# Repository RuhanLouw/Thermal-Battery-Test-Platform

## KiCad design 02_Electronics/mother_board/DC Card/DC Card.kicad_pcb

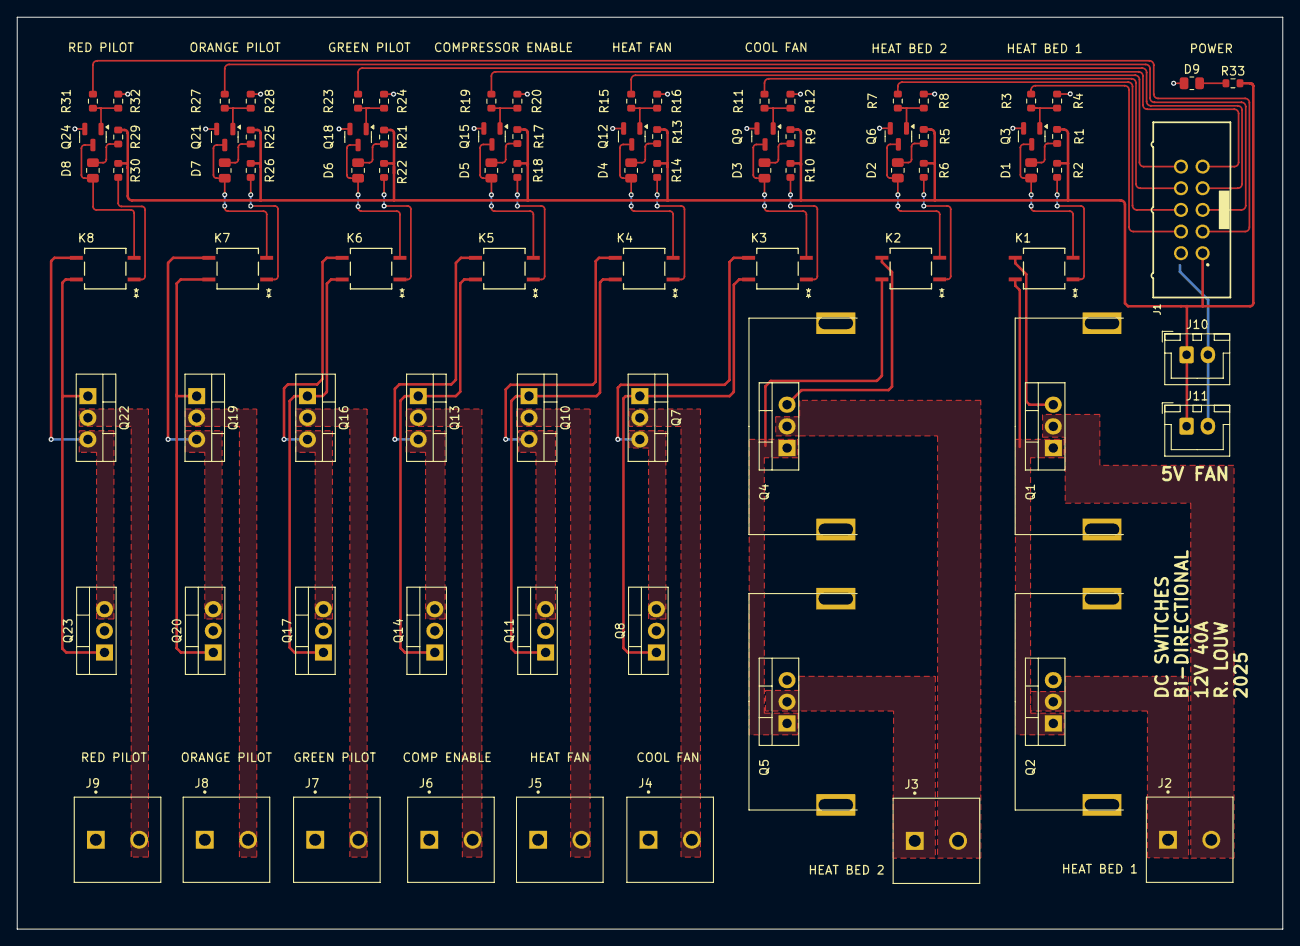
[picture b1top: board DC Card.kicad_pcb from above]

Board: 2 copper layers, 148.5 x 107.0 mm, 85 parts (0 on the bottom side), 75 nets.

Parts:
D1, D2, D3, D4, D5, D6, D7, D8, D9: LED; R_0805_2012Metric
J1: 61201021621
J2, J3, J4, J5, J6, J7, J8, J9: SW Conn; TE_282857-2_screw
J10, J11: Conn_01x02; JST_XH_B2B-XH-A_1x02_P2.50mm_Vertical
K1, K2, K3, K4, K5, K6, K7, K8: APV1121S; SOP4PIN_PAN-M
Q1, Q2, Q4, Q5: IRFB7545PBF; HSS-B20-NPR-02 heatsink
Q3, Q6, Q9, Q12, Q15, Q18, Q21, Q24: BSS138L; SOT-23
Q7, Q8, Q10, Q11, Q13, Q14, Q16, Q17, Q19, Q20, Q22, Q23: IRFB7545PBF; TO-220-3_Vertical
R1, R5, R9, R13, R17, R21, R25, R29: 145; R_0603_1608Metric
R2, R6, R10, R14, R18, R22, R26, R30: 182; R_0603_1608Metric
R3, R7, R11, R15, R19, R23, R27, R31: 300; R_0603_1608Metric
R4, R8, R12, R16, R20, R24, R28, R32: 10k; R_0603_1608Metric
R33: 150; R_0603_1608Metric

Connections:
5V_{DD}: J1.1, J10.1, J11.1, R1.2, R2.1, R5.2, R6.1, R9.2, R10.1, R13.2, R14.1, R17.2, R18.1, R21.2, R22.1, R25.2, R26.1, R29.2, R30.1, R33.2
/DC Switch_1/SWa: J3.1, Q5.2 (D)
/DC Switch_1/SWb: J3.2, Q4.2 (D)
/DC Switch_2/SWa: J4.1, Q8.2 (D)
/DC Switch_2/SWb: J4.2, Q7.2 (D)
/DC Switch_3/SWa: J5.1, Q11.2 (D)
/DC Switch_3/SWb: J5.2, Q10.2 (D)
/DC Switch_4/SWa: J6.1, Q14.2 (D)
/DC Switch_4/SWb: J6.2, Q13.2 (D)
/DC Switch_5/SWa: J7.1, Q17.2 (D)
/DC Switch_5/SWb: J7.2, Q16.2 (D)
/DC Switch_6/SWa: J8.1, Q20.2 (D)
/DC Switch_6/SWb: J8.2, Q19.2 (D)
/DC Switch_7/SWa: J9.1, Q23.2 (D)
/DC Switch_7/SWb: J9.2, Q22.2 (D)
/DC Switch_/SWa: J2.1, Q2.2 (D)
/DC Switch_/SWb: J2.2, Q1.2 (D)
DC Comp _EN: J1.9, R19.1
Evap FAN _PWM: J1.8, R11.1
GND_{DD}: D9.1 (K), J1.2, J10.2, J11.2, Q3.2 (S), Q6.2 (S), Q9.2 (S), Q12.2 (S), Q15.2 (S), Q18.2 (S), Q21.2 (S), Q24.2 (S), R4.2, R8.2, R12.2, R16.2, R20.2, R24.2, R28.2, R32.2
GREEN_PILOT _EN: J1.7, R23.1
HeatBed FAN _PWM: J1.10, R15.1
HeatBed_1 _PWM: J1.4, R3.1
HeatBed_2 _PWM: J1.6, R7.1
unnamed: D1.2 (A), R1.1
unnamed: D1.1 (K), K1.2, Q3.3 (D)
unnamed: D2.2 (A), R5.1
unnamed: D2.1 (K), K2.2, Q6.3 (D)
unnamed: D3.2 (A), R9.1
unnamed: D3.1 (K), K3.2, Q9.3 (D)
unnamed: D4.2 (A), R13.1
unnamed: D4.1 (K), K4.2, Q12.3 (D)
unnamed: D5.2 (A), R17.1
unnamed: D5.1 (K), K5.2, Q15.3 (D)
unnamed: D6.2 (A), R21.1
unnamed: D6.1 (K), K6.2, Q18.3 (D)
unnamed: D7.2 (A), R25.1
unnamed: D7.1 (K), K7.2, Q21.3 (D)
unnamed: D8.2 (A), R29.1
unnamed: D8.1 (K), K8.2, Q24.3 (D)
unnamed: D9.2 (A), R33.1
unnamed: K1.1, R2.2
unnamed: K2.1, R6.2
unnamed: K3.1, R10.2
unnamed: K4.1, R14.2
unnamed: K5.1, R18.2
unnamed: K6.1, R22.2
unnamed: K7.1, R26.2
unnamed: K8.1, R30.2
unnamed: K1.4, Q1.1 (G), Q2.1 (G)
unnamed: K1.3, Q1.3 (S), Q2.3 (S)
unnamed: Q3.1 (G), R3.2, R4.1
unnamed: K2.4, Q4.1 (G), Q5.1 (G)
unnamed: K2.3, Q4.3 (S), Q5.3 (S)
unnamed: Q6.1 (G), R7.2, R8.1
unnamed: K3.4, Q7.1 (G), Q8.1 (G)
unnamed: K3.3, Q7.3 (S), Q8.3 (S)
unnamed: Q9.1 (G), R11.2, R12.1
unnamed: K4.4, Q10.1 (G), Q11.1 (G)
unnamed: K4.3, Q10.3 (S), Q11.3 (S)
unnamed: Q12.1 (G), R15.2, R16.1
unnamed: K5.4, Q13.1 (G), Q14.1 (G)
unnamed: K5.3, Q13.3 (S), Q14.3 (S)
unnamed: Q15.1 (G), R19.2, R20.1
unnamed: K6.4, Q16.1 (G), Q17.1 (G)
unnamed: K6.3, Q16.3 (S), Q17.3 (S)
unnamed: Q18.1 (G), R23.2, R24.1
unnamed: K7.4, Q19.1 (G), Q20.1 (G)
unnamed: K7.3, Q19.3 (S), Q20.3 (S)
unnamed: Q21.1 (G), R27.2, R28.1
unnamed: K8.4, Q22.1 (G), Q23.1 (G)
unnamed: K8.3, Q22.3 (S), Q23.3 (S)
unnamed: Q24.1 (G), R31.2, R32.1
ORANGE_PILOT _EN: J1.5, R27.1
RED_PILOT _EN: J1.3, R31.1

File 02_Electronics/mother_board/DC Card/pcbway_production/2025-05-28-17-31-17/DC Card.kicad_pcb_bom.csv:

Designator,Quantity,Value,Footprint,Package,MPN,DNP,Mount_Type,Description
"D1, D2, D3, D4, D5, D6, D7, D8, D9",9,LED,R_0805_2012Metric,,,,smt,LED RED CLEAR 0805 SMD
J1,1,61201021621,61201021621,,,,tht,"Connector Header Through Hole 10 position 0.100"" (2.54mm)"
"J10, J11",2,Conn_01x02,JST_XH_B2B-XH-A_1x02_P2.50mm_Vertical,,,,tht,"Generic connector, single row, 01x02, script generated (kicad-library-utils/schlib/autogen/connector/)"
"J2, J3, J4, J5, J6, J7, J8, J9",8,SW Conn,TE_282857-2_screw,,,,tht,"Generic screw terminal, single row, 01x02, script generated (kicad-library-utils/schlib/autogen/connector/)"
"K1, K2, K3, K4, K5, K6, K7, K8",8,APV1121S,SOP4PIN_PAN-M,,,,smt,Optoisolator Photovoltaic Output 2500Vrms 1 Channel 4-SOP
"Q1, Q2, Q4, Q5",4,IRFB7545PBF,HSS-B20-NPR-02 heatsink,,,,tht,N-Channel 60 V 95A (Tc) 125W (Tc) Through Hole TO-220
"Q10, Q11, Q13, Q14, Q16, Q17, Q19, Q20, Q22, Q23, Q7, Q8",12,IRFB7545PBF,TO-220-3_Vertical,,,,tht,N-Channel 60 V 95A (Tc) 125W (Tc) Through Hole TO-220
"Q12, Q15, Q18, Q21, Q24, Q3, Q6, Q9",8,BSS138L,SOT-23,,,,smt,"50V Vds, 0.22A Id, N-Channel MOSFET, SOT-23"
"R1, R13, R17, R21, R25, R29, R5, R9",8,145,R_0603_1608Metric,,,,smt,RES 145 OHM 0.5% 1/10W 0603
"R10, R14, R18, R2, R22, R26, R30, R6",8,182,R_0603_1608Metric,,,,smt,RES 182 OHM 1% 1/10W 0603
"R11, R15, R19, R23, R27, R3, R31, R7",8,300,R_0603_1608Metric,,,,smt,RES SMD 300 OHM 5% 1/10W 0603
"R12, R16, R20, R24, R28, R32, R4, R8",8,10k,R_0603_1608Metric,,,,smt,RES 10K OHM 1% 1/10W 0603
R33,1,150,R_0603_1608Metric,,,,smt,RES SMD 150 OHM 0.1% 1/10W 0603

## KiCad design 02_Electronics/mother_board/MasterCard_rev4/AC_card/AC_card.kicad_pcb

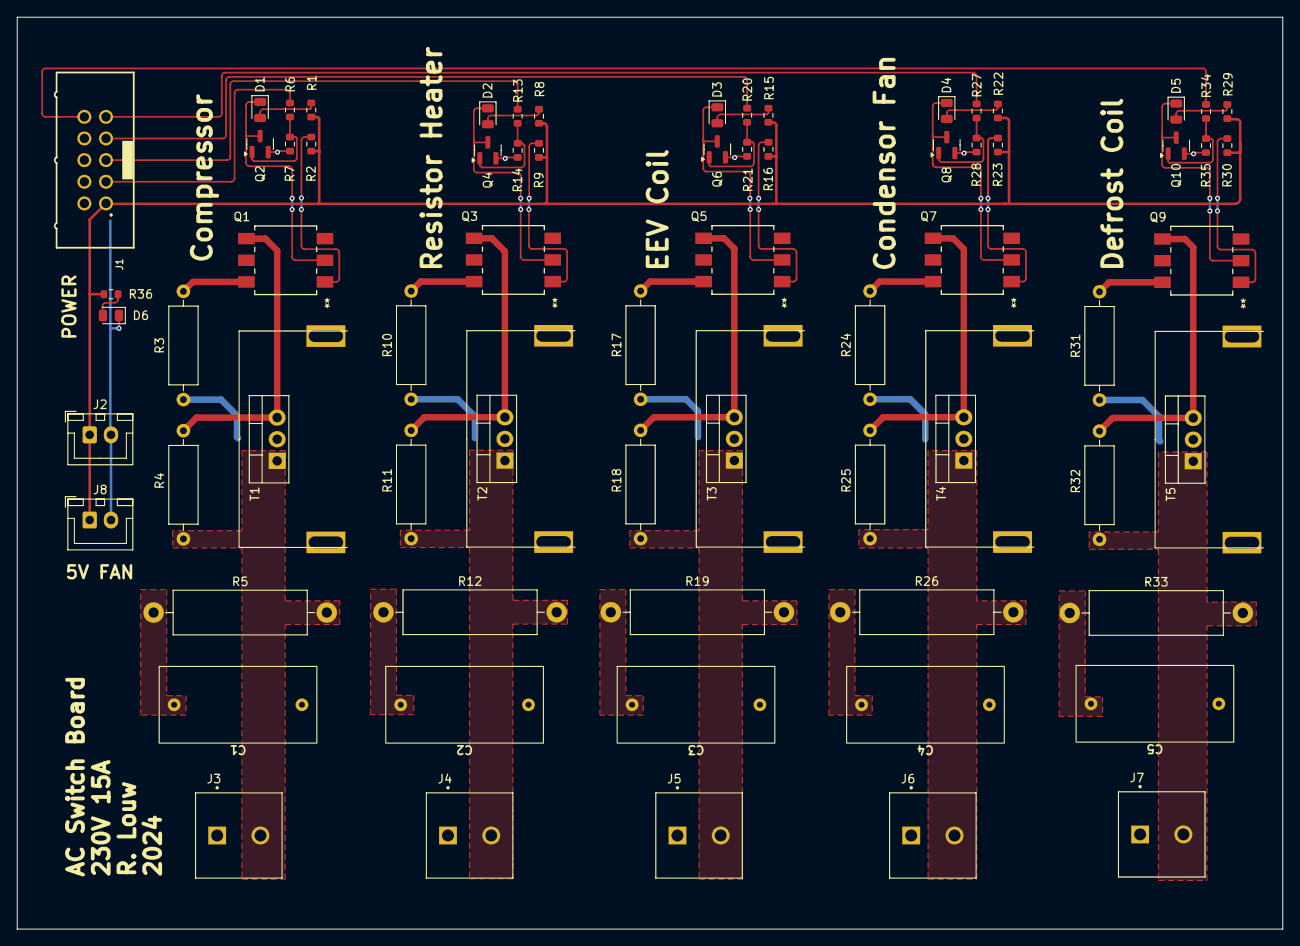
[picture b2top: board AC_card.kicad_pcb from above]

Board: 2 copper layers, 148.5 x 107.0 mm, 70 parts (0 on the bottom side), 53 nets.

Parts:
C1, C2, C3, C4, C5: 0.22u; CAP FILM 0.22UF 10 800VDC RAD
D1, D2, D3, D4, D5, D6: LED RED CLEAR 0805 SMD; LED_0805_2012Metric
J1: Control IN; 61201021621
J2, J8: Fan; JST_XH_B2B-XH-A_1x02_P2.50mm_Vertical
J3, J4, J5, J6, J7: Screw_Terminal_01x02; TE_282857-2_screw
Q1, Q3, Q5, Q7, Q9: MOC3063S-TA1; MOC306XS_LTO
Q2, Q4, Q6, Q8, Q10: BSS138L; SOT-23
R1, R8, R15, R22, R29, R36: 145; R_0603_1608Metric
R2, R9, R16, R23, R30: 182; R_0603_1608Metric
R3, R10, R17, R24, R31: 100; R_Axial_DIN0309_L9.0mm_D3.2mm_P12.70mm_Horizontal
R4, R11, R18, R25, R32: 390; R_Axial_DIN0309_L9.0mm_D3.2mm_P12.70mm_Horizontal
R5, R12, R19, R26, R33: 51; R_Axial_DIN0516_L15.5mm_D5.0mm_P20.32mm_Horizontal
R6, R13, R20, R27, R34: 300; R_0603_1608Metric
R7, R14, R21, R28, R35: 10k; R_0603_1608Metric
T1, T2, T3, T4, T5: BT138-800E,127; HSS-B20-NPR-02 heatsink

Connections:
5V_{DD}: J1.1, J2.1, J8.1, R1.2, R2.1, R8.2, R9.1, R15.2, R16.1, R22.2, R23.1, R29.2, R30.1, R36.2
/AC_SWITCH1/230VAC: C2.2, J4.1, R10.1, T2.2
/AC_SWITCH1/LOAD: J4.2, R11.2, R12.2, T2.1
/AC_SWITCH2/230VAC: C3.2, J5.1, R17.1, T3.2
/AC_SWITCH2/LOAD: J5.2, R18.2, R19.2, T3.1
/AC_SWITCH3/230VAC: C4.2, J6.1, R24.1, T4.2
/AC_SWITCH3/LOAD: J6.2, R25.2, R26.2, T4.1
/AC_SWITCH4/230VAC: C5.2, J7.1, R31.1, T5.2
/AC_SWITCH4/LOAD: J7.2, R32.2, R33.2, T5.1
/AC_SWITCH/230VAC: C1.2, J3.1, R3.1, T1.2
/AC_SWITCH/LOAD: J3.2, R4.2, R5.2, T1.1
AC COMP ENABLE: J1.3, R6.1
AC DEFROST ENABLE: J1.10, R34.1
AC EEV COIL ENABLE: J1.7, R20.1
AC FAN ENABLE: J1.9, R27.1
AC HEATER RESISTOR ENABLE: J1.5, R13.1
GND_{DD}: D6.1 (K), J1.2, J2.2, J8.2, Q2.2 (S), Q4.2 (S), Q6.2 (S), Q8.2 (S), Q10.2 (S), R7.2, R14.2, R21.2, R28.2, R35.2
unnamed: C1.1, R5.1
unnamed: C2.1, R12.1
unnamed: C3.1, R19.1
unnamed: C4.1, R26.1
unnamed: C5.1, R33.1
unnamed: D1.2 (A), R1.1
unnamed: D1.1 (K), Q1.2, Q2.3 (D)
unnamed: D2.2 (A), R8.1
unnamed: D2.1 (K), Q3.2, Q4.3 (D)
unnamed: D3.2 (A), R15.1
unnamed: D3.1 (K), Q5.2, Q6.3 (D)
unnamed: D4.2 (A), R22.1
unnamed: D4.1 (K), Q7.2, Q8.3 (D)
unnamed: D5.2 (A), R29.1
unnamed: D5.1 (K), Q9.2, Q10.3 (D)
unnamed: D6.2 (A), R36.1
unnamed: Q1.1, R2.2
unnamed: Q1.4, R4.1, T1.3
unnamed: Q1.6, R3.2
unnamed: Q2.1 (G), R6.2, R7.1
unnamed: Q3.1, R9.2
unnamed: Q3.4, R11.1, T2.3
unnamed: Q3.6, R10.2
unnamed: Q4.1 (G), R13.2, R14.1
unnamed: Q5.1, R16.2
unnamed: Q5.4, R18.1, T3.3
unnamed: Q5.6, R17.2
unnamed: Q6.1 (G), R20.2, R21.1
unnamed: Q7.1, R23.2
unnamed: Q7.4, R25.1, T4.3
unnamed: Q7.6, R24.2
unnamed: Q8.1 (G), R27.2, R28.1
unnamed: Q9.1, R30.2
unnamed: Q9.4, R32.1, T5.3
unnamed: Q9.6, R31.2
unnamed: Q10.1 (G), R34.2, R35.1

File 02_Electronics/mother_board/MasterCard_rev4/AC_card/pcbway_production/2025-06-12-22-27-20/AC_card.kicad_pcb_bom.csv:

Designator,Quantity,Value,Footprint,Package,MPN,DNP,Mount_Type,Description,PARTREV,STANDARD,MAXIMUM_PACKAGE_HEIGHT,MANUFACTURER
"C1, C2, C3, C4, C5",5,0.22u,CAP FILM 0.22UF 10 800VDC RAD,,,,tht,"0.22 µF Film Capacitor 650V 1600V (1.6kV) Polypropylene (PP), Metallized Radial",,,,
"D1, D2, D3, D4, D5, D6",6,LED RED CLEAR 0805 SMD,LED_0805_2012Metric,,,,smt,Red 625nm LED Indication - Discrete 2V 0805 (2012 Metric),,,,
J1,1,Control IN,61201021621,,,,tht,"Connector Header Through Hole 10 position 0.100"" (2.54mm)",,,,
"J2, J8",2,Fan,JST_XH_B2B-XH-A_1x02_P2.50mm_Vertical,,,,tht,"Generic connector, single row, 01x02, script generated (kicad-library-utils/schlib/autogen/connector/)",,,,
"J3, J4, J5, J6, J7",5,Screw_Terminal_01x02,TE_282857-2_screw,,,,tht,"Generic screw terminal, single row, 01x02, script generated (kicad-library-utils/schlib/autogen/connector/)",,,,
"Q1, Q3, Q5, Q7, Q9",5,MOC3063S-TA1,MOC306XS_LTO,,,,smt,,,,,
"Q10, Q2, Q4, Q6, Q8",5,BSS138L,SOT-23,,,,smt,MOSFET N-CH 50V 200MA SOT23-3,,,,
"R1, R15, R22, R29, R36, R8",6,145,R_0603_1608Metric,,,,smt,RES 145 OHM 0.5% 1/10W 0603,,,,
"R10, R17, R24, R3, R31",5,100,R_Axial_DIN0309_L9.0mm_D3.2mm_P12.70mm_Horizontal,,,,tht,"100 Ohms ±5% 0.5W, 1/2W Through Hole Resistor Axial Carbon Film",,,,
"R11, R18, R25, R32, R4",5,390,R_Axial_DIN0309_L9.0mm_D3.2mm_P12.70mm_Horizontal,,,,tht,RES 390 OHM 5% 1/2W AXIAL,,,,
"R12, R19, R26, R33, R5",5,51,R_Axial_DIN0516_L15.5mm_D5.0mm_P20.32mm_Horizontal,,,,tht,"51 Ohms ±5% 3W Through Hole Resistor Axial Flame Retardant Coating, Pulse Withstanding, Safety Metal Film",,,,
"R13, R20, R27, R34, R6",5,300,R_0603_1608Metric,,,,smt,RES SMD 300 OHM 5% 1/10W 0603,,,,
"R14, R21, R28, R35, R7",5,10k,R_0603_1608Metric,,,,smt,RES 10K OHM 1% 1/10W 0603,,,,
"R16, R2, R23, R30, R9",5,182,R_0603_1608Metric,,,,smt,RES 182 OHM 1% 1/10W 0603,,,,
"T1, T2, T3, T4, T5",5,"BT138-800E,127",HSS-B20-NPR-02 heatsink,,,,tht,TRIAC SENS GATE 800V 12A TO220AB,02,IPC 7351B,19.35 mm,WeEn Semiconductors

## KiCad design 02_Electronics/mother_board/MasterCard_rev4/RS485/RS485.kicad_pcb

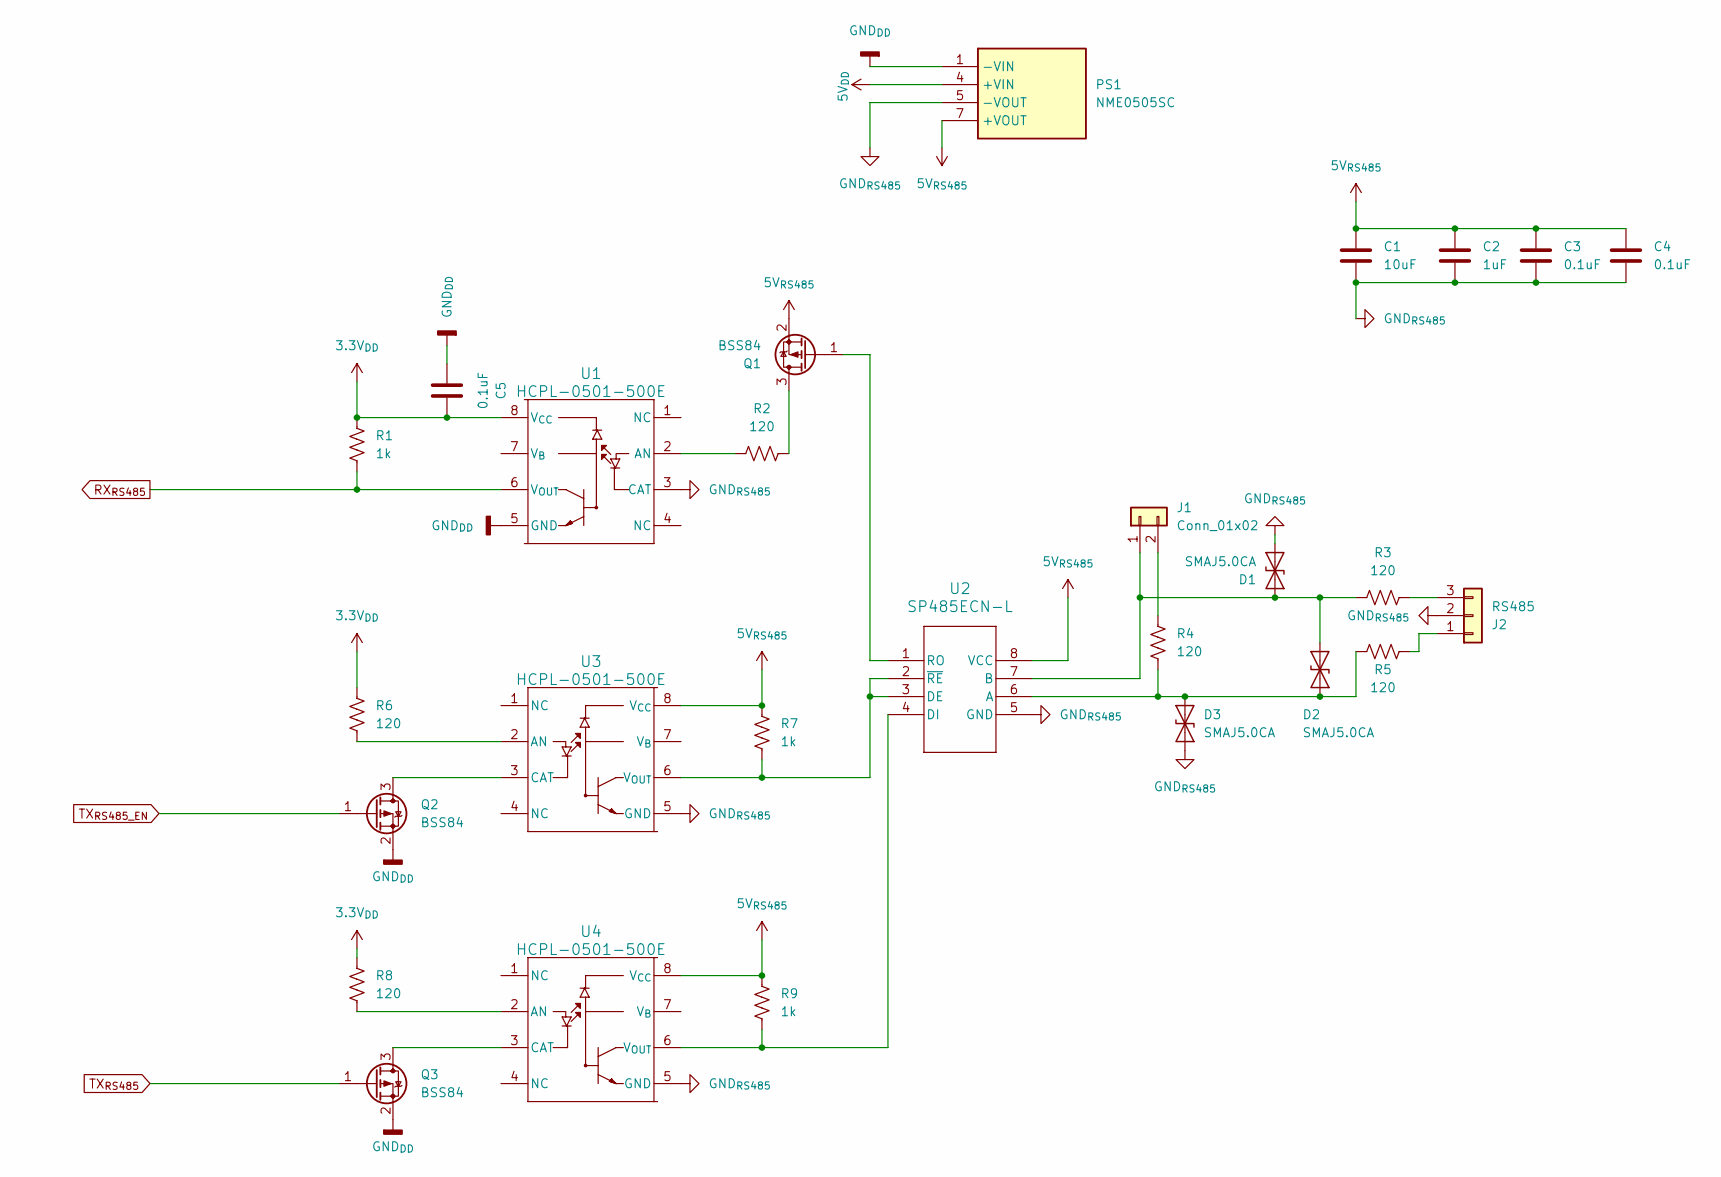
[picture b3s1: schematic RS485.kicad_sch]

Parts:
C1: 10uF; C_0805_2012Metric
C2: 1uF; C_0603_1608Metric
C3, C4, C5: 0.1uF; C_0603_1608Metric
D1, D2, D3: SMAJ5.0CA; D_SMA
J1: Conn_01x02; PinHeader_1x02_P2.54mm_Vertical
J2: RS485; TE_282857-3_screw
PS1: NME0505SC; Mouser Part Number 580-NME0505SC
Q1, Q2, Q3: BSS84; SOT-23
R1, R7, R9: 1k; R_0603_1608Metric
R2, R6, R8: 120; R_0603_1608Metric
R3, R4, R5: 120; R_1206_3216Metric
U1, U3, U4: HCPL-0501-500E; SO8_HCPL-0501-500_BRA
U2: SP485ECN-L; NSOIC-8

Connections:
3.3V_{DD}: C5.2, R1.2, R6.1, R8.1, U1.8 (V_{CC})
5V_{DD}: PS1.4 (+VIN)
5V_{RS485}: C1.1, C2.1, C3.1, C4.1, PS1.7 (+VOUT), Q1.2 (S), R7.2, R9.2, U2.8 (VCC), U3.8 (V_{CC}), U4.8 (V_{CC})
GND_{DD}: C5.1, PS1.1 (-VIN), Q2.2 (S), Q3.2 (S), U1.5 (GND)
GND_{RS485}: C1.2, C2.2, C3.2, C4.2, D1.1 (A1), D3.1 (A1), J2.2, PS1.5 (-VOUT), U1.3 (CAT), U2.5 (GND), U3.5 (GND), U4.5 (GND)
unnamed: D1.2 (A2), D2.1 (A1), J1.1, R3.1, U2.7 (B)
unnamed: D2.2 (A2), D3.2 (A2), R4.2, R5.1, U2.6 (A)
unnamed: J1.2, R4.1
unnamed: J2.1, R5.2
unnamed: J2.3, R3.2
unnamed: Q1.3 (D), R2.1
unnamed: Q1.1 (G), U2.1 (RO)
unnamed: Q2.3 (D), U3.3 (CAT)
unnamed: Q3.3 (D), U4.3 (CAT)
unnamed: R2.2, U1.2 (AN)
unnamed: R7.1, U2.2 (~RE), U2.3 (DE), U3.6 (V_{OUT})
unnamed: R9.1, U2.4 (DI), U4.6 (V_{OUT})
unnamed: R6.2, U3.2 (AN)
unnamed: R8.2, U4.2 (AN)
RX_{RS485}: R1.1, U1.6 (V_{OUT})
TX_{RS485_EN}: Q2.1 (G)
TX_{RS485}: Q3.1 (G)

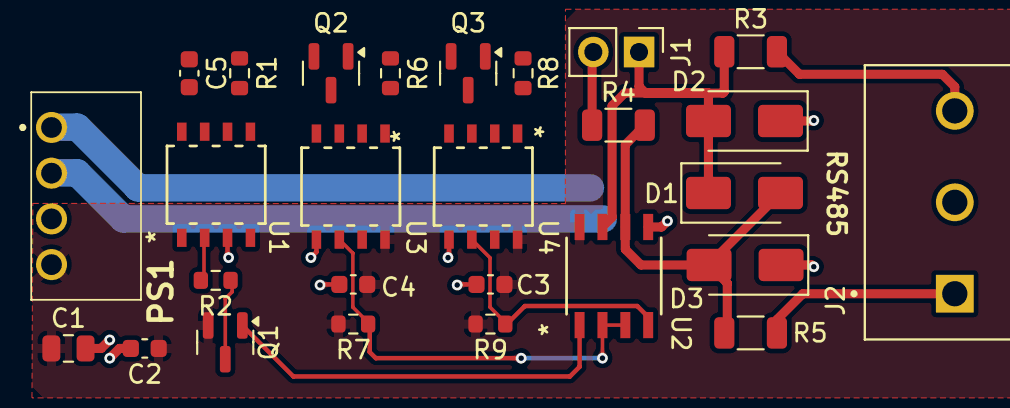
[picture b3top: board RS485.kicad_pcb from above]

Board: 2 copper layers, 27 parts (0 on the bottom side), 19 nets.

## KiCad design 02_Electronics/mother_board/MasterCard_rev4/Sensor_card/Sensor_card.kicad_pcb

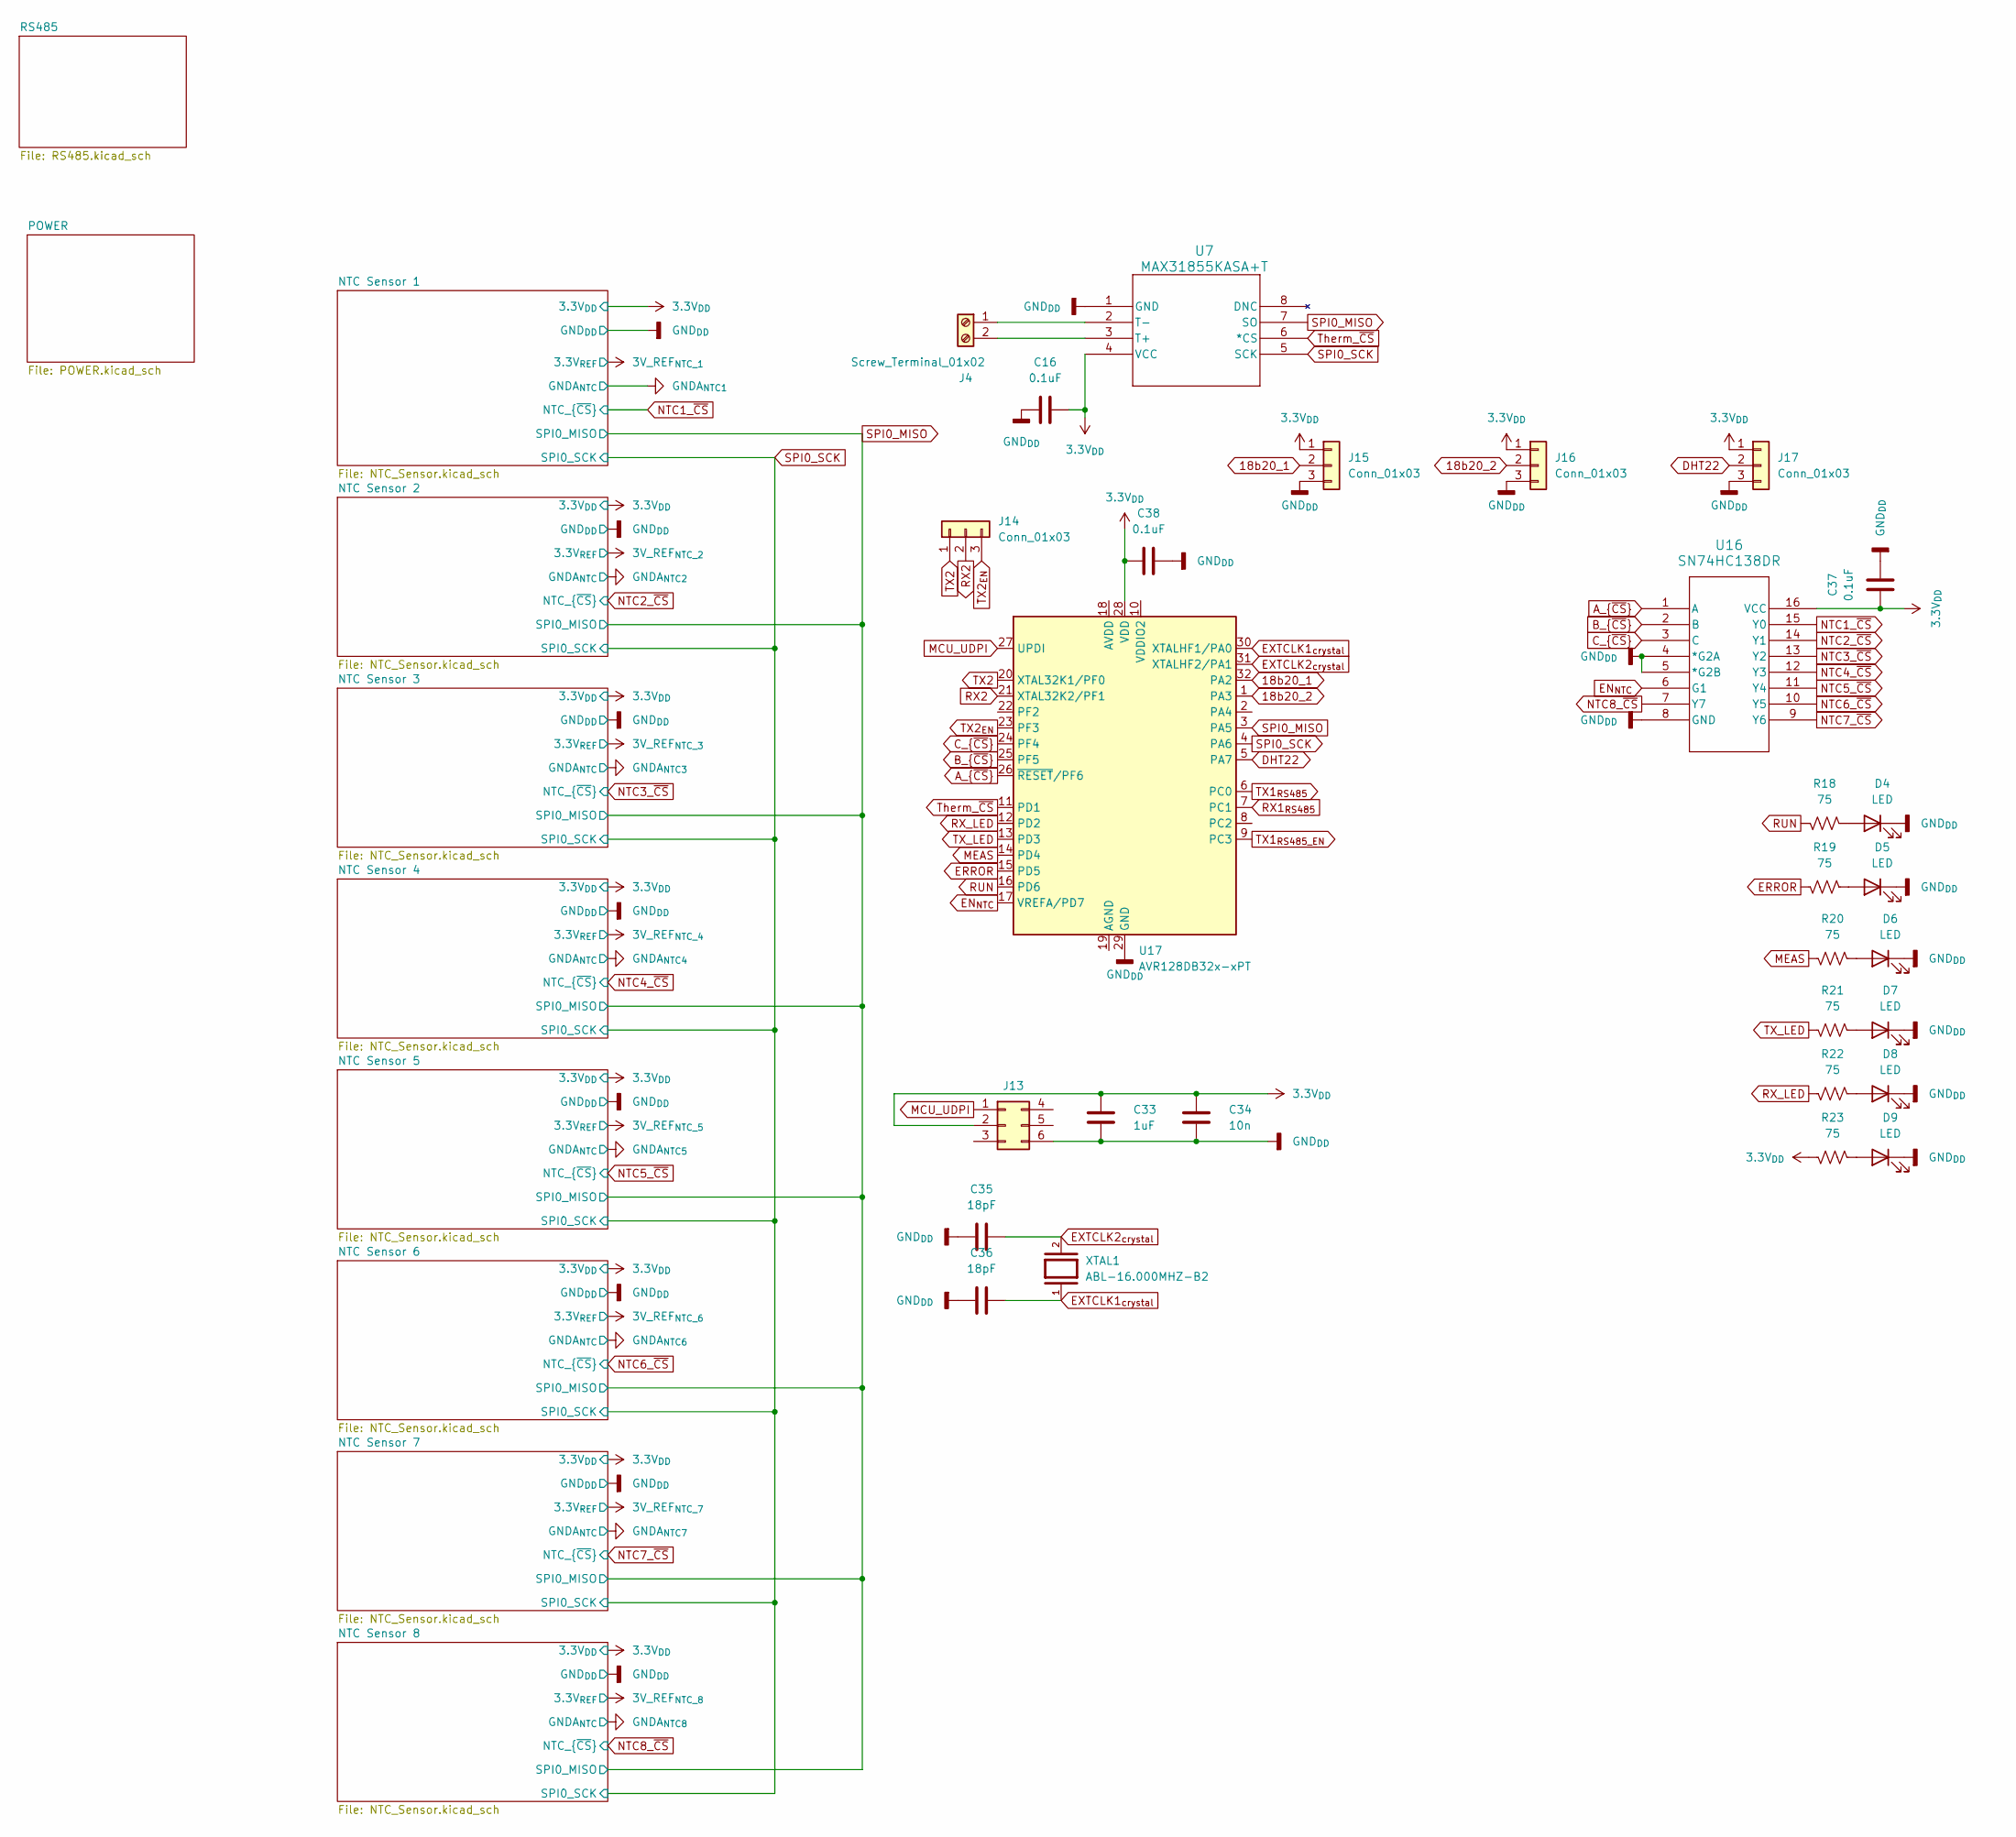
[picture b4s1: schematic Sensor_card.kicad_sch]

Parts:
C16, C37, C38: 0.1uF; C_0603_1608Metric
C33: 1uF; C_0603_1608Metric
C34: 10n; C_0603_1608Metric
C35, C36: 18pF; C_0402_1005Metric
D4, D5, D6, D7, D8, D9: LED; LED_0805_2012Metric
J4: Screw_Terminal_01x02; TE_282857-2_screw
J13: Conn_02x03_Top_Bottom; 61200621621
J14: Conn_01x03; PinHeader_1x03_P2.54mm_Vertical
J15, J16, J17: Conn_01x03; JST_XH_B3B-XH-A_1x03_P2.50mm_Vertical
R18, R19, R20, R21, R22, R23: 75; R_0603_1608Metric
U7: MAX31855KASA+T; 21-0041B_8_MXM
U16: SN74HC138DR
U17: AVR128DB32x-xPT; TQFP-32_7x7mm_P0.8mm
XTAL1: ABL-16.000MHZ-B2; XTAL_HC49P488W46L1150T500H350; PARTREV 03.27.2018

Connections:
3.3V_{DD}: C16.2, C33.1, C34.1, C37.1, C38.1, J13.2, J15.1, J16.1, J17.1, R23.1, U7.4 (VCC), U16.16 (VCC), U17.28 (VDD); also elsewhere on the board
18b20_1: J15.2, U17.32 (PA2)
18b20_2: J16.2, U17.1 (PA3)
A_{~CS}: U16.1 (A), U17.26 (~RESET/PF6)
B_{~CS}: U16.2 (B), U17.25 (PF5)
C_{~CS}: U16.3 (C), U17.24 (PF4)
DHT22: J17.2, U17.5 (PA7)
EN_{NTC}: U16.6 (G1), U17.17 (VREFA/PD7)
ERROR: R19.1, U17.15 (PD5)
EXTCLK1_{crystal}: C36.1, U17.30 (XTALHF1/PA0), XTAL1.1
EXTCLK2_{crystal}: C35.1, U17.31 (XTALHF2/PA1), XTAL1.2
GND_{DD}: C16.1, C33.2, C34.2, C35.2, C36.2, C37.2, C38.2, D4.1 (K), D5.1 (K), D6.1 (K), D7.1 (K), D8.1 (K), D9.1 (K), J13.6, J14.4, J15.3, J16.3, J17.3, U7.1 (GND), U16.4 (*G2A), U16.5 (*G2B), U16.8 (GND), U17.29 (GND); also elsewhere on the board
MCU_UDPI: J13.1, U17.27 (UPDI)
MEAS: R20.1, U17.14 (PD4)
NTC1_~CS: U16.15 (Y0); also elsewhere on the board
NTC2_~CS: U16.14 (Y1); also elsewhere on the board
NTC3_~CS: U16.13 (Y2); also elsewhere on the board
NTC4_~CS: U16.12 (Y3); also elsewhere on the board
NTC5_~CS: U16.11 (Y4); also elsewhere on the board
NTC6_~CS: U16.10 (Y5); also elsewhere on the board
NTC7_~CS: U16.9 (Y6); also elsewhere on the board
NTC8_~CS: U16.7 (Y7); also elsewhere on the board
unnamed: D4.2 (A), R18.2
unnamed: D5.2 (A), R19.2
unnamed: D6.2 (A), R20.2
unnamed: D7.2 (A), R21.2
unnamed: D8.2 (A), R22.2
unnamed: D9.2 (A), R23.2
unnamed: J4.1, U7.2 (T-)
unnamed: J4.2, U7.3 (T+)
RUN: R18.1, U17.16 (PD6)
RX1_{RS485}: U17.7 (PC1); also elsewhere on the board
RX2: J14.2, U17.21 (XTAL32K2/PF1)
RX_LED: R22.1, U17.12 (PD2)
SPI0_MISO: U7.7 (SO), U17.3 (PA5); also elsewhere on the board
SPI0_SCK: U7.5 (SCK), U17.4 (PA6); also elsewhere on the board
TX1_{RS485_EN}: U17.9 (PC3); also elsewhere on the board
TX1_{RS485}: U17.6 (PC0); also elsewhere on the board
TX2: J14.1, U17.20 (XTAL32K1/PF0)
TX2_{EN}: J14.3, U17.23 (PF3)
TX_LED: R21.1, U17.13 (PD3)
Therm_~CS: U7.6 (*CS), U17.11 (PD1)

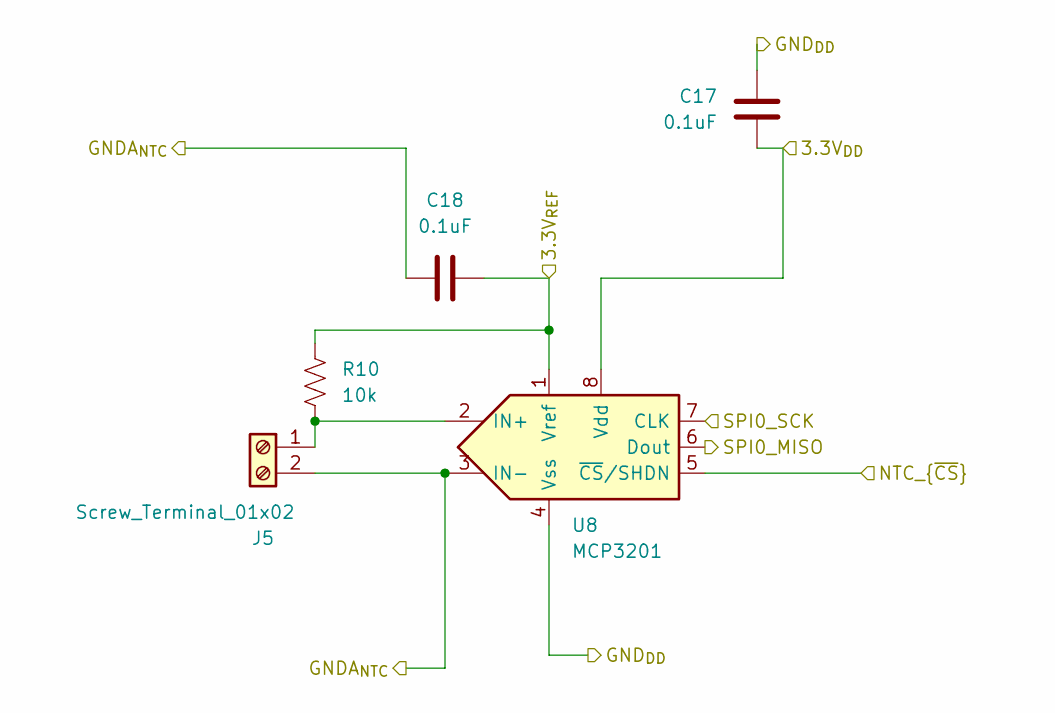
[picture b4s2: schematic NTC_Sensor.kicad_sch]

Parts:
C17, C18: 0.1uF; C_0603_1608Metric
J5: Screw_Terminal_01x02; TERM BLOCK 2P HORIZON 2.54MM PCB
R10: 10k; R_1206_3216Metric
U8: MCP3201; SOIC8-N_MC_MCH

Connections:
3.3V_{DD}: C17.2, U8.8 (Vdd); also elsewhere on the board
3V_REF_{NTC_1}: C18.2, R10.1, U8.1 (Vref); also elsewhere on the board
GNDA_{NTC1}: C18.1, J5.2, U8.3 (IN-); also elsewhere on the board
GND_{DD}: C17.1, U8.4 (Vss); also elsewhere on the board
NTC1_~CS: U8.5 (~CS/SHDN); also elsewhere on the board
unnamed: J5.1, R10.2, U8.2 (IN+)
SPI0_MISO: U8.6 (Dout); also elsewhere on the board
SPI0_SCK: U8.7 (CLK); also elsewhere on the board

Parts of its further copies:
C19, C20, C21, C22, C23, C24, C25, C26, C27, C28, C29, C30, C31, C32: 0.1uF; C_0603_1608Metric
J6, J7, J8, J9, J10, J11, J12: Screw_Terminal_01x02; TERM BLOCK 2P HORIZON 2.54MM PCB
R11, R12, R13, R14, R15, R16, R17: 10k; R_1206_3216Metric
U9, U10, U11, U12, U13, U14, U15: MCP3201; SOIC8-N_MC_MCH

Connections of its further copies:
3.3V_{DD}: C19.2, C21.2, C23.2, C25.2, C27.2, C29.2, C31.2, U9.8 (Vdd), U10.8 (Vdd), U11.8 (Vdd), U12.8 (Vdd), U13.8 (Vdd), U14.8 (Vdd), U15.8 (Vdd); also elsewhere on the board
3V_REF_{NTC_2}: C20.2, R11.1, U9.1 (Vref); also elsewhere on the board
3V_REF_{NTC_3}: C22.2, R12.1, U10.1 (Vref); also elsewhere on the board
3V_REF_{NTC_4}: C24.2, R13.1, U11.1 (Vref); also elsewhere on the board
3V_REF_{NTC_5}: C26.2, R14.1, U12.1 (Vref); also elsewhere on the board
3V_REF_{NTC_6}: C28.2, R15.1, U13.1 (Vref); also elsewhere on the board
3V_REF_{NTC_7}: C30.2, R16.1, U14.1 (Vref); also elsewhere on the board
3V_REF_{NTC_8}: C32.2, R17.1, U15.1 (Vref); also elsewhere on the board
GNDA_{NTC2}: C20.1, J6.2, U9.3 (IN-); also elsewhere on the board
GNDA_{NTC3}: C22.1, J7.2, U10.3 (IN-); also elsewhere on the board
GNDA_{NTC4}: C24.1, J8.2, U11.3 (IN-); also elsewhere on the board
GNDA_{NTC5}: C26.1, J9.2, U12.3 (IN-); also elsewhere on the board
GNDA_{NTC6}: C28.1, J10.2, U13.3 (IN-); also elsewhere on the board
GNDA_{NTC7}: C30.1, J11.2, U14.3 (IN-); also elsewhere on the board
GNDA_{NTC8}: C32.1, J12.2, U15.3 (IN-); also elsewhere on the board
GND_{DD}: C19.1, C21.1, C23.1, C25.1, C27.1, C29.1, C31.1, U9.4 (Vss), U10.4 (Vss), U11.4 (Vss), U12.4 (Vss), U13.4 (Vss), U14.4 (Vss), U15.4 (Vss); also elsewhere on the board
NTC2_~CS: U9.5 (~CS/SHDN); also elsewhere on the board
NTC3_~CS: U10.5 (~CS/SHDN); also elsewhere on the board
NTC4_~CS: U11.5 (~CS/SHDN); also elsewhere on the board
NTC5_~CS: U12.5 (~CS/SHDN); also elsewhere on the board
NTC6_~CS: U13.5 (~CS/SHDN); also elsewhere on the board
NTC7_~CS: U14.5 (~CS/SHDN); also elsewhere on the board
NTC8_~CS: U15.5 (~CS/SHDN); also elsewhere on the board
unnamed: J6.1, R11.2, U9.2 (IN+)
unnamed: J7.1, R12.2, U10.2 (IN+)
unnamed: J8.1, R13.2, U11.2 (IN+)
unnamed: J9.1, R14.2, U12.2 (IN+)
unnamed: J10.1, R15.2, U13.2 (IN+)
unnamed: J11.1, R16.2, U14.2 (IN+)
unnamed: J12.1, R17.2, U15.2 (IN+)
SPI0_MISO: U9.6 (Dout), U10.6 (Dout), U11.6 (Dout), U12.6 (Dout), U13.6 (Dout), U14.6 (Dout), U15.6 (Dout); also elsewhere on the board
SPI0_SCK: U9.7 (CLK), U10.7 (CLK), U11.7 (CLK), U12.7 (CLK), U13.7 (CLK), U14.7 (CLK), U15.7 (CLK); also elsewhere on the board

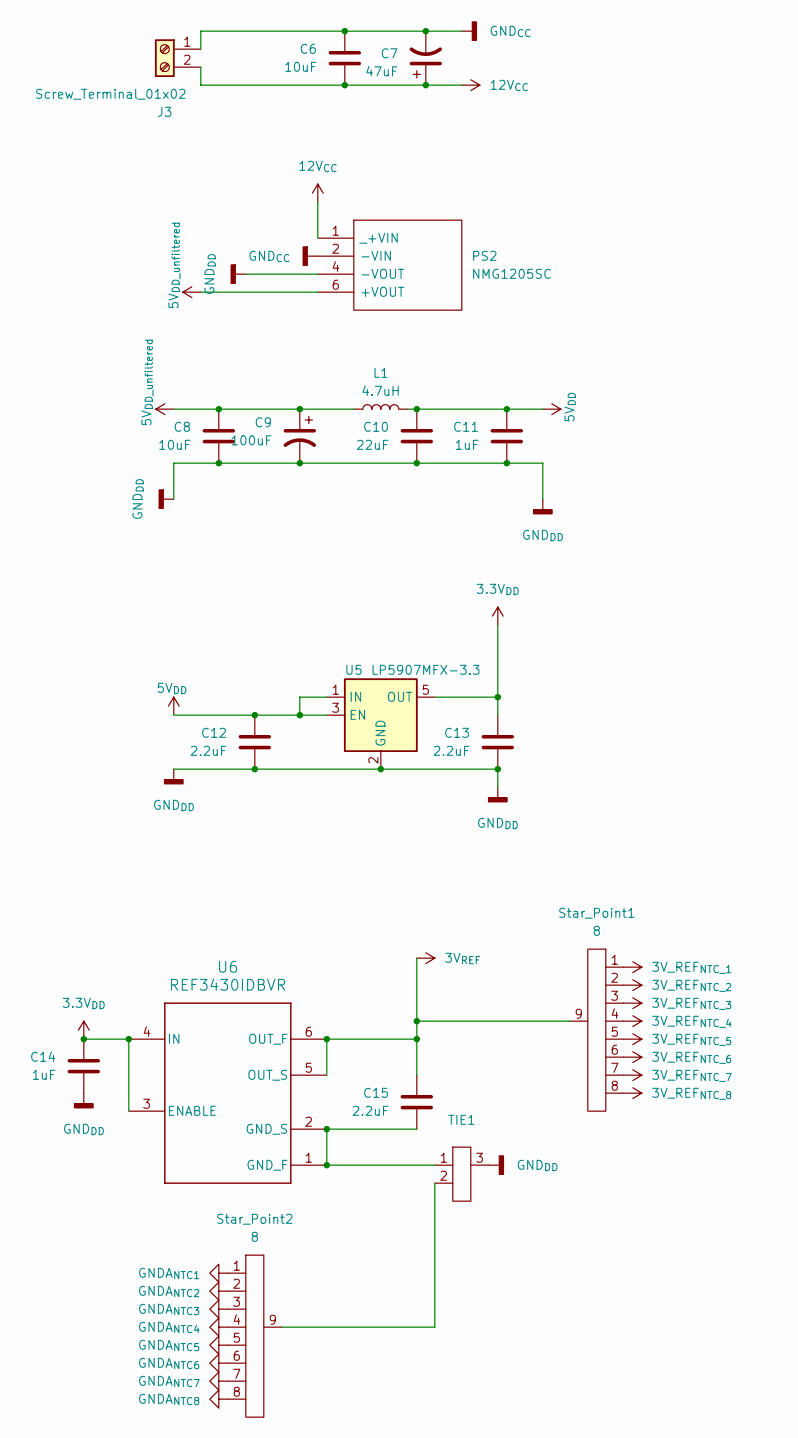
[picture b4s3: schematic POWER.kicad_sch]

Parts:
C6, C8: 10uF; C_0805_2012Metric
C7: 47uF; WCAP-ASLI_6.3X5.5_DXL_47uF
C9: 100uF; C_Radial_D6.3mm_H11.0mm_P2.50mm
C10: 22uF; C_1210_3225Metric
C11, C14: 1uF; C_0603_1608Metric
C12, C13, C15: 2.2uF; C_0603_1608Metric
J3: Screw_Terminal_01x02; TE_282857-2_screw
L1: 4.7uH; L_1210_3225Metric_Pad1.42x2.65mm_HandSolder_cad
PS2: NMG1205SC
Star_Point1, Star_Point2: 8; STARPOINT 9 ROUND PAD
TIE1: Star_Point_3
U5: LP5907MFX-3.3; SOT-23-5
U6: REF3430IDBVR; SOT-23-6

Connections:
3.3V_{DD}: C13.1, C14.1, U5.5 (OUT), U6.3 (ENABLE), U6.4 (IN); also elsewhere on the board
3V_REF_{NTC_1}: Star_Point1.1 (tie_1); also elsewhere on the board
3V_REF_{NTC_2}: Star_Point1.2 (tie_2); also elsewhere on the board
3V_REF_{NTC_3}: Star_Point1.3 (tie_3); also elsewhere on the board
3V_REF_{NTC_4}: Star_Point1.4 (tie_3); also elsewhere on the board
3V_REF_{NTC_5}: Star_Point1.5; also elsewhere on the board
3V_REF_{NTC_6}: Star_Point1.6; also elsewhere on the board
3V_REF_{NTC_7}: Star_Point1.7; also elsewhere on the board
3V_REF_{NTC_8}: Star_Point1.8; also elsewhere on the board
3V_{REF}: C15.1, Star_Point1.9, U6.5 (OUT_S), U6.6 (OUT_F)
5V_{DD_unfiltered}: C8.1, C9.1, L1.2, PS2.6 (+VOUT); also elsewhere on the board
5V_{DD}: C10.1, C11.1, C12.1, L1.1, U5.1 (IN), U5.3 (EN)
12V_{CC}: C6.2, C7.1, J3.2, PS2.1 (_+VIN)
GNDA_{NTC1}: Star_Point2.1 (tie_1); also elsewhere on the board
GNDA_{NTC2}: Star_Point2.2 (tie_2); also elsewhere on the board
GNDA_{NTC3}: Star_Point2.3 (tie_3); also elsewhere on the board
GNDA_{NTC4}: Star_Point2.4 (tie_3); also elsewhere on the board
GNDA_{NTC5}: Star_Point2.5; also elsewhere on the board
GNDA_{NTC6}: Star_Point2.6; also elsewhere on the board
GNDA_{NTC7}: Star_Point2.7; also elsewhere on the board
GNDA_{NTC8}: Star_Point2.8; also elsewhere on the board
GND_{CC}: C6.1, C7.2, J3.1, PS2.2 (-VIN)
GND_{DD}: C8.2, C9.2, C10.2, C11.2, C12.2, C13.2, C14.2, PS2.4 (-VOUT), TIE1.3 (tie_3), U5.2 (GND); also elsewhere on the board
unnamed: C15.2, TIE1.1 (tie_1), U6.1 (GND_F), U6.2 (GND_S)
unnamed: Star_Point2.9, TIE1.2 (tie_2)
